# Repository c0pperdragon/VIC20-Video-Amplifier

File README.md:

# VIC20-Video-Amplifier
Modify the analog video circuit of a VIC 20 to use modern parts

## Project intentions

My main intention here was to learn about the video generation circuitry of the VIC-20
and maybe come up with some way to interface it with a RGBtoHDMI to generate HDMI.

While I did not succeed in reliably quantizing the analog signal back to its digital
form, I did make some improvements on the overall analog circuit. 
 
## Replace original video amplifier with sockets

To make experimenting simpler, I just went and totally removed all components involved
in amplifying the video signal from the VIC. On my board (cost reduced small variant) this is realtively
easy, as the empty contact holes next to the VIC directly carry GND, +5V and both luma and chroma.
These are now broken out with a pin socket (using 4 of the 7 contacts). On the other side sockets are 
prepared to receive 3 signals to be forwarded to the A/V connector on pin 1, 4 and 5. 

## Cabling on the underside

Using 3 now unused holes (all parts are removed here so the traces do not matter) the pin sockets
on the front side are forwarded with wires to the A/V connector. Also the PCB trace between 
pin 4 and pin 5 under the connector and between pin 1 and 5V had to be cut. 

## Insert an amplifier PCB

I designed a PCB that carries a modern video amplifier IC and its supporting passive components to
fit the prepared pin sockets. 

Two trimmer potentiometers are provided to independently adjust the brightness and the color saturation.

A voltage regulator is used to get a stable reference voltage to drive the VIC's luma output DAC. 
This should provide the most noise-free signal possible.
 
## Modified A/V pinout

| Pin  | Signal    |
| ---- | --------- |
| 1    | Luminance |
| 2    | Ground    |
| 3    | Audio     |
| 4    | Composite |
| 5    | Chroma    |

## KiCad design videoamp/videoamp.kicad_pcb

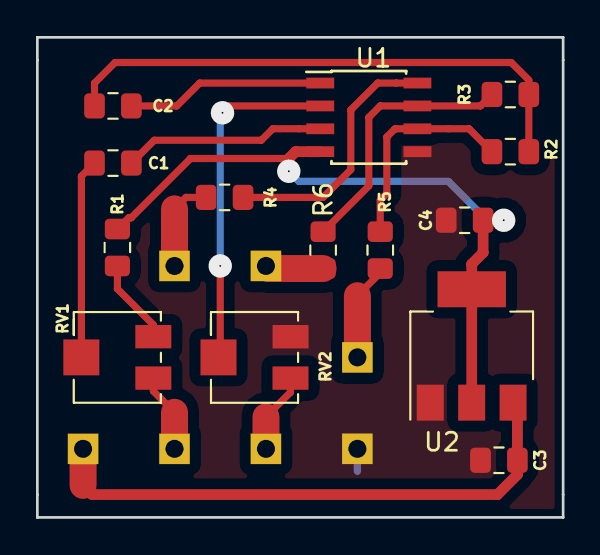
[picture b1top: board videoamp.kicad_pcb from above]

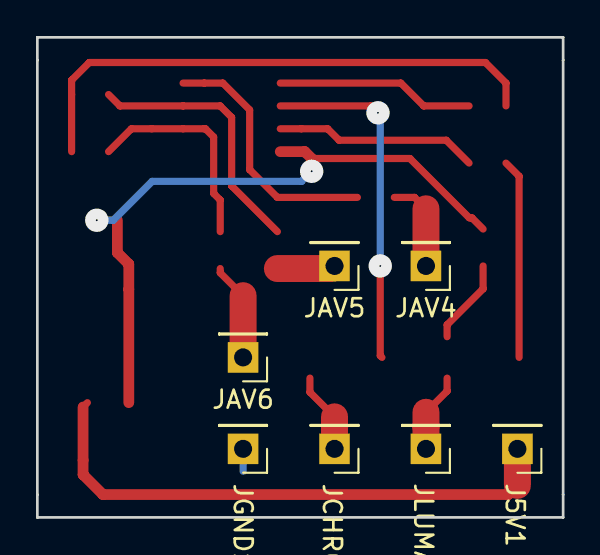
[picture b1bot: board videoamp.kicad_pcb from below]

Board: 2 copper layers, 29.2 x 26.7 mm, 21 parts (7 on the bottom side), 17 nets.

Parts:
C1, C2: 100nF; C_0805_2012Metric_Pad1.15x1.40mm_HandSolder
C3, C4: 1uF; C_0805_2012Metric_Pad1.15x1.40mm_HandSolder
J5V1: Conn_01x01; PinHeader_1x01_P2.54mm_Vertical
JAV4, JAV5, JAV6: Conn_01x01; PinHeader_1x01_P2.54mm_Vertical
JCHROMA1: Conn_01x01; PinHeader_1x01_P2.54mm_Vertical
JGND1: Conn_01x01; PinHeader_1x01_P2.54mm_Vertical
JLUMA1: Conn_01x01; PinHeader_1x01_P2.54mm_Vertical
R1: 100; R_0805_2012Metric_Pad1.15x1.40mm_HandSolder
R2, R3: 1k; R_0805_2012Metric_Pad1.15x1.40mm_HandSolder
R4, R5, R6: 75; R_0805_2012Metric_Pad1.15x1.40mm_HandSolder
RV1, RV2: 500; Potentiometer_Bourns_3224J_Horizontal
U1: THS7316; SOIC-8_3.9x4.9mm_P1.27mm
U2: AMS1117-3.3; SOT-223-3_TabPin2

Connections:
+3V3: C4.1, R1.1, U1.4, U2.2
+5V: C3.1, J5V1.1, U2.3
/CHROMA: R3.2, R5.2, U1.7
/COMPOSITE: R4.2, U1.8
/LUMA: R2.2, R6.2, U1.6
GND: C3.2, C4.2, JGND1.1, RV2.1, U1.5, U2.1
unnamed: C1.1, RV1.2
unnamed: C1.2, U1.3
unnamed: C2.1, R2.1, R3.1
unnamed: C2.2, U1.1
unnamed: JAV4.1, R4.1
unnamed: JAV5.1, R5.1
unnamed: JAV6.1, R6.1
unnamed: JCHROMA1.1, RV2.3
unnamed: JLUMA1.1, RV1.3
unnamed: R1.2, RV1.1
unnamed: RV2.2, U1.2

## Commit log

2022-01-29 Clean up the PCB a bit
2022-01-29 Documentation and pictures
2022-01-29 Typos
2022-08-25 Redesign board to provide luma/chroma/composite signals on A/V out
